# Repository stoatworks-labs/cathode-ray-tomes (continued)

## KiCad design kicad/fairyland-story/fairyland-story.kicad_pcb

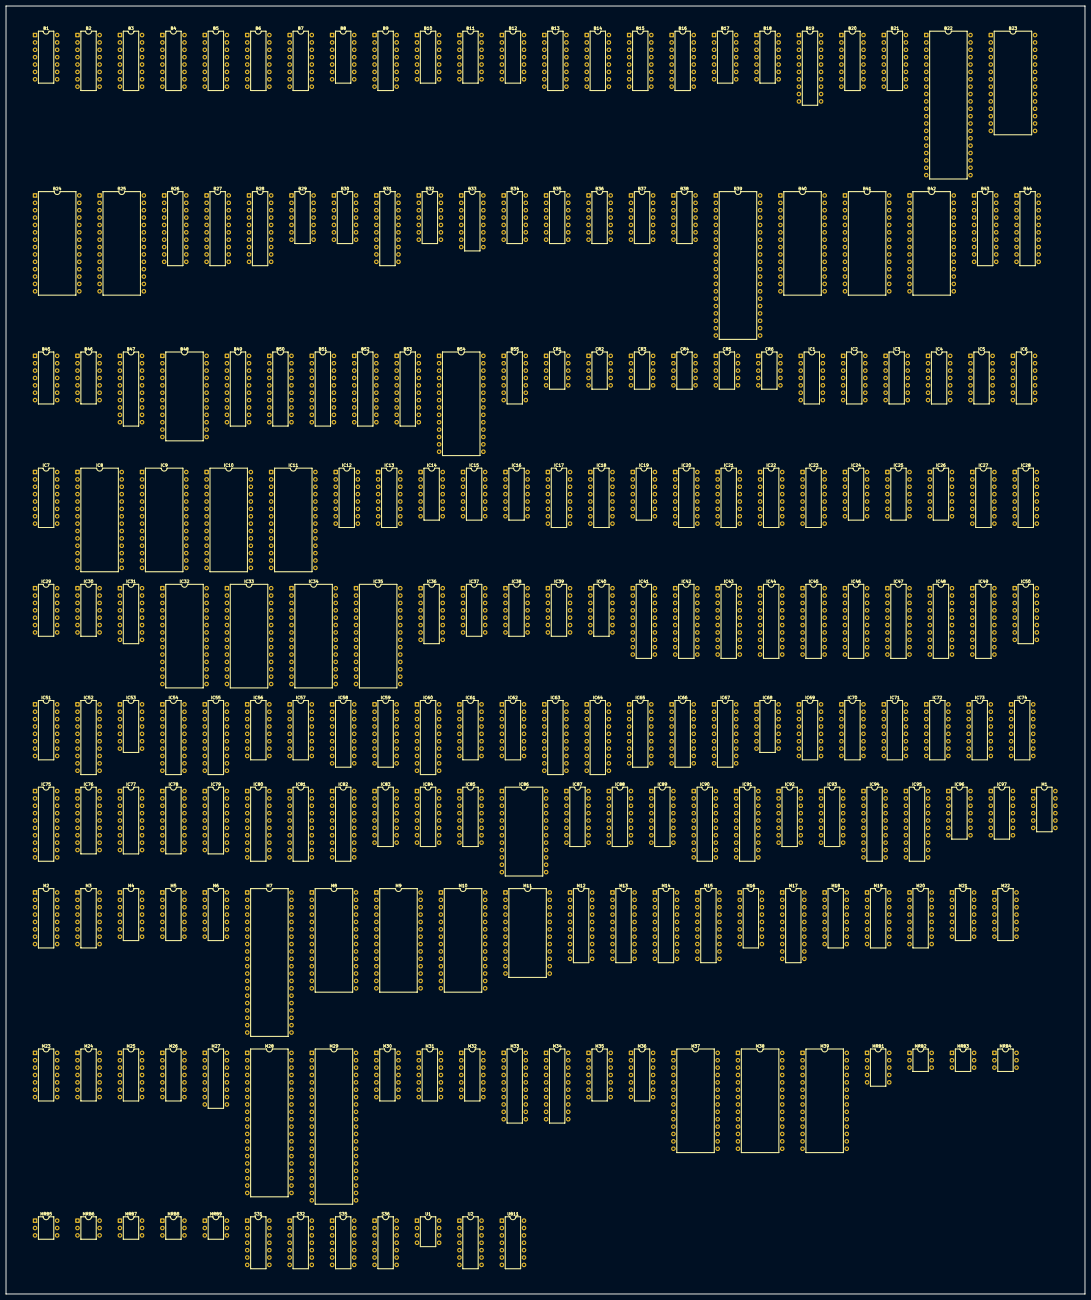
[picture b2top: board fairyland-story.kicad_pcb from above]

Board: 2 copper layers, 371.7 x 443.7 mm, 213 parts (0 on the bottom side), 719 nets, no tracks yet.

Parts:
B1, B11: 74LS07; DIP-14_W7.62mm
B2: 74LS175; DIP-16_W7.62mm
B3: MC14584B; DIP-16_W7.62mm
B4: TD62003P; DIP-16_W7.62mm
B5, B6, B7, B13, B14, B15: 74LS251; DIP-16_W7.62mm
B8: 74LS393; DIP-14_W7.62mm
B9: 74LS155; DIP-16_W7.62mm
B10, B29: 74LS08; DIP-14_W7.62mm
B12, B34, B35, B36, B37, B46: 74LS74; DIP-14_W7.62mm
B16: 74LS253; DIP-16_W7.62mm
B17, B45: 74LS04; DIP-14_W7.62mm
B18: 74LS10; DIP-14_W7.62mm
B19, B31, B47, B49, B50, B51: 74LS244; DIP-20_W7.62mm
B20, B21, B33: 74LS139; DIP-16_W7.62mm
B22, B39: Z80CPU; DIP-40_W15.24mm
B23, B24, B25, B40, B41, B42: 27128; DIP-28_W15.24mm
B26, B27, B28: 74LS245; DIP-20_W7.62mm
B30: 74LS00; DIP-14_W7.62mm
B32, B55: 74LS02; DIP-14_W7.62mm
B38: 74LS32; DIP-14_W7.62mm
B43, B44, B52, B53: 74LS374; DIP-20_W7.62mm
B48: TMM2018_25_35_45; DIP-24_W15.24mm
B54: MC68705P5S; DIP-28_W15.24mm
CR1, CR2, CR3, CR4, CR5, CR6: XXCRXXXX; DIP-10_W7.62mm
IC1, IC29, IC37: 74LS04; DIP-14_W7.62mm
IC2: 74LS107; DIP-14_W7.62mm
IC3, IC5, IC14, IC19, IC24: 74LS74; DIP-14_W7.62mm
IC4: 74LS125; DIP-14_W7.62mm
IC6, IC16, IC26, IC30, IC38, IC39: 74LS86; DIP-14_W7.62mm
IC7, IC21, IC31, IC61, IC62: 74LS298; DIP-16_W7.62mm
IC8, IC9, IC10, IC11, IC32, IC33, IC34, IC35: 27128; DIP-28_W15.24mm
IC12, IC13, IC22, IC23: 74LS194; DIP-16_W7.62mm
IC15, IC68, IC96: 74LS08; DIP-14_W7.62mm
IC17, IC18, IC27, IC28: 74LS161; DIP-16_W7.62mm
IC20, IC89: 74LS139; DIP-16_W7.62mm
IC25: 74LS10; DIP-14_W7.62mm
IC36: 74LS158; DIP-16_W7.62mm
IC40: 74LS20; DIP-14_W7.62mm
IC41, IC42: 74LS373; DIP-20_W7.62mm
IC43, IC46, IC47, IC52, IC54, IC55: 74LS273; DIP-20_W7.62mm
IC44, IC48, IC63, IC64, IC81, IC95: 74LS374; DIP-20_W7.62mm
IC45, IC90, IC91, IC94: 74LS245; DIP-20_W7.62mm
IC49, IC60, IC75, IC80, IC82: 74LS244; DIP-20_W7.62mm
IC50, IC51: 74LS669; DIP-16_W7.62mm
IC53, IC97: 74LS32; DIP-14_W7.62mm
IC56, IC57: 74LS283; DIP-16_W7.62mm
IC58, IC59, IC65, IC66, IC67, IC76, IC77, IC78, IC79: MBM2148; DIP-18_W7.62mm
IC69: 74LS257; DIP-16_W7.62mm
IC70: 74LS42; DIP-16_W7.62mm
IC71, IC83, IC84, IC85: 74LS157; DIP-16_W7.62mm
IC72, IC73, IC87, IC88: 74LS253; DIP-16_W7.62mm
IC74: 74LS191; DIP-16_W7.62mm
IC86: RAM_2016; DIP-24_W15.24mm
IC92, IC93: 74LS174; DIP-16_W7.62mm
M1: SB3731; DIP-12_W7.62mm
M2, M3: TA7630P; DIP-16_W7.62mm
M4, M5, M6: MC3301P; DIP-14_W7.62mm
M7: Z80CPU; DIP-40_W15.24mm
M8, M9, M10, M37, M38, M39: 2764; DIP-28_W15.24mm
M11: MSM2128-20RS; DIP-24_W15.24mm
M12, M13, M15, M17: 74LS374; DIP-20_W7.62mm
M14, M33, M34: 74LS273; DIP-20_W7.62mm
M16: 74LS367; DIP-16_W7.62mm
M18, M20: 74LS139; DIP-16_W7.62mm
M19: 74LS138; DIP-16_W7.62mm
M21: 74LS32; DIP-14_W7.62mm
M22, M24, M25, M26, M30, M35: 74LS74; DIP-14_W7.62mm
M23: 74LS08; DIP-14_W7.62mm
M27: 74LS155; DIP-16_W7.62mm
M28: YM2149; DIP-40_W15.24mm
M29: MSM5232RS; DIP-42_W15.24mm
M31, M32: 74LS393; DIP-14_W7.62mm
M36: 74LS04; DIP-14_W7.62mm
MRB1: DIP-10_W7.62mm
MRB2, MRB3, MRB4, MRB5, MRB6, MRB7, MRB8, MRB9: DIP-6_W7.62mm
S31, S32: 74LS393; DIP-14_W7.62mm
S35: 74LS74; DIP-14_W7.62mm
S36: 74LS04; DIP-14_W7.62mm
U1: MC1455P; DIP-8_W7.62mm
U2: 74LS07; DIP-14_W7.62mm
UB11: 74LS07; DIP-14_W7.62mm

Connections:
+12V: B1.14, B2.16, B3.14, B3.16, B4.9, B5.16, B6.16, B7.16, B8.14, B9.16, B10.14, B12.1, B12.14, B13.16, B14.16, B15.16, B16.16, B17.14, B18.14, B19.20, B21.16, B22.11, B23.1, B23.28, B24.1, B24.28, B25.1, B25.28, B29.14, B30.14, B31.20, B32.14, B33.16, B34.14, B35.1, B35.13, B35.14, B36.1, B36.13, B36.14, B37.1, B37.13, B37.14, B38.14, B39.11, B40.1, B40.28, B41.1, B41.28, B42.1, B42.28, B45.14, B46.1, B46.4, B46.10, B46.13, B46.14, B47.20, B48.24, B49.20, B50.20, B51.20, B54.3, B54.6, B55.14, CR1.1, CR2.1, CR3.1, CR4.1, CR5.1, CR6.1, IC1.14, IC2.4, IC2.10, IC2.11, IC2.13, IC2.14, IC3.1, IC3.4, IC3.13, IC5.1, IC5.4, IC5.10, IC5.13, IC5.14, IC6.14, IC7.16, IC8.1, IC8.27, IC8.28, IC9.1, IC9.27, IC9.28, IC10.1, IC10.27, IC10.28, IC11.1, IC11.27, IC11.28, IC12.1, IC13.1, IC14.4, IC14.14, IC15.14, IC16.14, IC17.1, IC17.5, IC17.6, IC18.1, IC18.9, IC19.4, IC19.10, IC19.13, IC20.16, IC21.16, IC22.1, IC23.1, IC24.1, IC24.10, IC24.13, IC24.14, IC25.11, IC25.14, IC26.14, IC27.1, IC27.3, IC27.4, IC27.5, IC28.1, IC28.5, IC29.14, IC30.14, IC31.6, IC31.16, IC32.1, IC32.27, IC32.28, IC33.1, IC33.27, IC33.28, IC34.1, IC34.27, IC34.28, IC35.1, IC35.27, IC35.28, IC36.16, IC37.14, IC38.14, IC39.14, IC40.14, IC41.20, IC42.20, IC43.1, IC46.1, IC47.1, IC49.20, IC50.16, IC51.16, IC53.14, IC54.1, IC55.1, IC58.18, IC59.18, IC60.20, IC61.16, IC62.16, IC65.18, IC66.18, IC67.18, IC68.14, IC69.2, IC69.5, IC70.16, IC71.2, IC71.5, IC71.13, IC72.16, IC73.3, IC73.4, IC73.10, IC73.12, IC73.13, IC73.16, IC74.1, IC74.5, IC74.10, IC74.15, IC74.16, IC75.20, IC76.18, IC77.18, IC78.18, IC79.18, IC80.20, IC82.20, IC83.13, IC87.16, IC88.4, IC88.13, IC88.16, IC89.16, IC92.16, IC93.16, IC96.14, IC97.14, M2.12, M3.12, M4.14, M5.14, M6.14, M7.11, M8.1, M8.27, M8.28, M9.1, M9.27, M9.28, M10.1, M10.27, M10.28, M11.24, M14.1, M16.16, M18.16, M19.6, M20.16, M21.14, M22.10, M22.14, M23.14, M26.1, M26.10, M26.13, M26.14, M27.16, M28.25, M28.28, M28.40, M30.4, M30.10, M30.12, M30.14, M33.1, M34.1, M35.4, M35.10, M35.13, M37.1, M37.27, M37.28, M38.1, M38.27, M38.28, M39.1, M39.27, M39.28, S31.14, S32.14, S35.14, S36.14, U1.4, U1.8
/COINLOCK: B2.2, B11.1, B11.13
/Cabinet/CR1P_BTN_1: B14.15, CR6.2
/Cabinet/CR1P_BTN_2: B13.15, CR6.6
/Cabinet/CR1P_DOWN: B7.15, CR3.4
/Cabinet/CR1P_LEFT: B5.15, CR3.8
/Cabinet/CR1P_RIGHT: B6.15, CR3.6
/Cabinet/CR1P_START: B13.1, CR1.2
/Cabinet/CR1P_UP: B15.15, CR3.2
/Cabinet/CR2P_BTN_1: B14.13, CR6.4
/Cabinet/CR2P_BTN_2: B13.13, CR6.8
/Cabinet/CR2P_DOWN: B7.13, CR2.4
/Cabinet/CR2P_LEFT: B5.13, CR2.8
/Cabinet/CR2P_RIGHT: B6.13, CR2.6
/Cabinet/CR2P_START: B14.1, CR1.4
/Cabinet/CR2P_UP: B15.13, CR2.2
/Cabinet/CRNC1: B15.12, CR5.2
/Cabinet/CRNC2: B7.12, CR5.4
/Cabinet/CRNC3: B6.12, CR5.6
/Cabinet/CRNC4: B5.12, CR5.8
/Cabinet/CRNC5: B15.14, CR4.2
/Cabinet/CRNC6: B7.14, CR4.4
/Cabinet/CRNC7: B6.14, CR4.6
/Cabinet/CRNC8: B5.14, CR4.8
/Cabinet/CRSERVICE: B15.1, CR1.6
/Cabinet/CRTILT: B7.1, CR1.8
/Cabinet/~COINA: B10.6, B11.5
/Cabinet/~COINAB: B4.1, B4.2, B5.1, B11.6
/Cabinet/~COINB: B10.8, B11.9
/Cabinet/~COINBB: B4.4, B4.5, B6.1, B11.8
/Cabinet/~COIN_2: B3.6, B16.13
/MAB0: B39.30, B40.10, B41.10, B42.10, B43.9, B49.2
/MAB1: B39.31, B40.9, B41.9, B42.9, B43.12, B49.4
/MAB2: B39.32, B40.8, B41.8, B42.8, B43.6, B49.6
/MAB3: B39.33, B40.7, B41.7, B42.7, B43.15, B49.8
/MAB4: B39.34, B40.6, B41.6, B42.6, B43.5, B50.2
/MAB5: B39.35, B40.5, B41.5, B42.5, B43.16, B50.4
/MAB6: B39.36, B40.4, B41.4, B42.4, B43.2, B50.6
/MAB7: B39.37, B40.3, B41.3, B42.3, B43.19, B50.8
/MAB8: B39.38, B40.25, B41.25, B42.25, B44.9, B51.2
/MAB9: B39.39, B40.24, B41.24, B42.24, B44.12, B51.4
/MAB10: B39.40, B40.21, B41.21, B42.21, B44.6, B51.6
/MAB11: B39.1, B40.23, B41.23, B42.23, B44.15, B51.8
/MAB12: B19.11, B21.2, B39.2, B40.2, B41.2, B42.2, B44.5
/MAB13: B21.3, B39.3, B40.26, B41.26, B42.26, B44.16
/MAB14: B21.14, B39.4, B44.2
/MAB15: B21.13, B39.5, B44.19
/MD0: B27.9, B28.11, B39.14, B40.11, B41.11, B42.11
/MD1: B27.8, B28.12, B39.15, B40.12, B41.12, B42.12
/MD2: B27.7, B28.13, B39.12, B40.13, B41.13, B42.13
/MD3: B27.6, B28.14, B39.8, B40.15, B41.15, B42.15
/MD4: B27.5, B28.15, B39.7, B40.16, B41.16, B42.16
/MD5: B27.4, B28.16, B39.9, B40.17, B41.17, B42.17
/MD6: B27.3, B28.17, B39.10, B40.18, B41.18, B42.18
/MD7: B27.2, B28.18, B39.13, B40.19, B41.19, B42.19
/Main/CLK5: B46.9, B47.6
/Main/MCU/IBF: B12.9, B54.8
/Main/MCU/PA0: B28.9, B43.8, B44.8, B52.8, B53.12, B54.20
/Main/MCU/PA1: B28.8, B43.13, B44.13, B52.13, B53.9, B54.21
/Main/MCU/PA2: B28.7, B43.7, B44.7, B52.7, B53.15, B54.22
/Main/MCU/PA3: B28.6, B43.14, B44.14, B52.14, B53.6, B54.23
/Main/MCU/PA4: B28.5, B43.4, B44.4, B52.4, B53.16, B54.24
/Main/MCU/PA5: B28.4, B43.17, B44.17, B52.17, B53.5, B54.25
/Main/MCU/PA6: B28.3, B43.3, B44.3, B52.3, B53.19, B54.26
/Main/MCU/PA7: B28.2, B43.18, B44.18, B52.18, B53.2, B54.27
/Main/MCU/~ALE0: B43.11, B54.18
/Main/MCU/~ALE1: B44.11, B54.19
/Main/MCU/~LRD: B12.11, B53.1, B54.13
/Main/MCU/~LWR: B12.3, B52.11, B54.14
/Main/MCU/~OBF: B12.5, B54.9
/Main/MQpC: B30.2, B30.10, B32.13, B36.10
/Main/MxC: B30.1, B34.5
/Main/SMRQ: B30.4, B30.13, B32.1
/Main/SWAIT: B29.1, B35.9
/Main/~BUSRQ: B18.2, B39.25, B54.15
/Main/~CLK5: B46.8, B46.12, B47.8
/Main/~CLK5*: B34.11, B36.11, B47.4, B47.12
/Main/~CRD: B47.15, B54.17
/Main/~CWR: B28.1, B47.17, B54.16
/Main/~INT: B37.9, B39.16
/Main/~IORQ: B38.12, B39.20
/Main/~M1: B38.13, B39.27
/Main/~MCLK: B39.6, B46.3, B47.18
/Main/~MCU: B18.1, B28.19, B43.1, B44.1, B46.6, B47.19, B54.10
/Main/~MMpC: B17.1, B21.1, B21.9, B32.12
/Main/~MMx0: B21.12, B40.20
/Main/~MMx4: B21.11, B41.20
/Main/~MMx8: B21.10, B42.20
/Main/~MREQ: B32.11, B39.19, B47.7
/Main/~MSpC': B34.13, B35.3
/Main/~MxC: B30.9, B34.6, B35.10
/Main/~SOECLK: B34.3, B47.2, B47.14
/OBF: B12.6, B14.14
/SBA0: B22.30, B23.10, B24.10, B25.10, B49.17
/SBA1: B22.31, B23.9, B24.9, B25.9, B49.15
/SBA2: B22.32, B23.8, B24.8, B25.8, B49.13
/SBA3: B22.33, B23.7, B24.7, B25.7, B49.11
/SBA4: B22.34, B23.6, B24.6, B25.6, B50.17
/SBA5: B22.35, B23.5, B24.5, B25.5, B50.15
/SBA6: B22.36, B23.4, B24.4, B25.4, B50.13
/SBA7: B22.37, B23.3, B24.3, B25.3, B50.11
/SBA8: B22.38, B23.25, B24.25, B25.25, B51.11
/SBA9: B22.39, B23.24, B24.24, B25.24, B51.13
/SBA10: B22.40, B23.21, B24.21, B25.21, B51.15
/SBA11: B22.1, B23.23, B24.23, B25.23, B51.17
/SBA12: B19.8, B22.2, B23.2, B24.2, B25.2, B33.2
/SBA13: B22.3, B23.26, B24.26, B25.26, B33.3
/SBA14: B22.4, B33.13
/SBA15: B22.5, B33.14
/SBCLK: B22.6, B47.16
/SBD0: B22.14, B23.11, B24.11, B25.11, B26.9
/SBD1: B22.15, B23.12, B24.12, B25.12, B26.8
/SBD2: B22.12, B23.13, B24.13, B25.13, B26.7
/SBD3: B22.8, B23.15, B24.15, B25.15, B26.6
/SBD4: B22.7, B23.16, B24.16, B25.16, B26.5
/SBD5: B22.9, B23.17, B24.17, B25.17, B26.4
/SBD6: B22.10, B23.18, B24.18, B25.18, B26.3
/SBD7: B22.13, B23.19, B24.19, B25.19, B26.2
/SHAB0: B5.11, B6.11, B7.11, B9.13, B13.11, B14.11, B15.11, B16.14, B48.8, B49.3, B49.18, IC60.2, IC75.8, IC80.8, IC85.2, IC89.14, M18.2, M18.14
/SHAB1: B5.10, B6.10, B7.10, B9.3, B13.10, B14.10, B15.10, B16.2, B48.7, B49.5, B49.16, IC60.4, IC75.6, IC80.6, IC85.5, IC89.13
/SHAB2: B5.9, B6.9, B7.9, B13.9, B14.9, B15.9, B48.6, B49.7, B49.14, IC60.6, IC75.4, IC80.4, IC85.11
/SHAB3: B48.5, B49.9, B49.12, IC60.8, IC75.2, IC80.2, IC85.14
/SHAB4: B48.4, B50.3, B50.18, IC60.11, IC75.17, IC80.17, IC84.2
/SHAB5: B48.3, B50.5, B50.16, IC60.13, IC75.15, IC80.15, IC84.5
/SHAB6: B48.2, B50.7, B50.14, IC60.15, IC75.13, IC80.13, IC84.11
/SHAB7: B48.1, B50.9, B50.12, IC60.17, IC75.11, IC80.11, IC84.14
/SHAB8: B48.23, B51.3, B51.18, IC83.2, IC89.2
/SHAB9: B48.22, B51.5, B51.16, IC83.5, IC89.3
/SHAB10: B20.2, B48.19, B51.7, B51.14, IC83.11
/SHAB11: B20.3, B51.9, B51.12
/SHDB0: B2.4, B13.5, B26.18, B27.18, B48.9, B52.9, B53.13
/SHDB1: B2.5, B14.5, B26.17, B27.17, B48.10, B52.12, B53.8
/SHDB2: B2.12, B15.5, B26.16, B27.16, B48.11, B52.6, B53.14
/SHDB3: B2.13, B7.5, B26.15, B27.15, B48.13, B52.15, B53.7
/SHDB4: B6.5, B26.14, B27.14, B48.14, B52.5, B53.17
/SHDB5: B5.5, B26.13, B27.13, B48.15, B52.16, B53.4
/SHDB6: B16.7, B26.12, B27.12, B48.16, B52.2, B53.18
/SHDB7: B16.9, B26.11, B27.11, B48.17, B52.19, B53.3
/Shared/?: B31.5, B31.16
/Shared/~CTL: B2.9, B9.5
/Shared/~SHACS: B19.5, B19.16, B48.18
/Sound/AMUTE: M1.6, M22.9
/Sound/AVSS: M29.23, M29.32
/Sound/CLK2: M28.22, M29.19, M29.20, M32.3
/Sound/CLK4: M29.13, M35.5
/Sound/Latches/~NMIdis: M22.3, M27.11
/Sound/Latches/~NMIsen: M22.4, M22.11, M27.10
/Sound/Latches/~RST_CS: M18.5, M30.3
/Sound/Latches/~SD2SH: M15.11, M25.10, M27.9
/Sound/Latches/~SDCHK: M12.1, M25.3, M27.7
/Sound/Latches/~SDOE': M13.1, M27.4
/Sound/Latches/~SDST: M16.1, M27.6
/Sound/Latches/~SH2SD: M12.11, M18.4, M25.4
/Sound/Latches/~SHA3: M17.11, M24.4
/Sound/Latches/~SHAOE3: M17.1, M24.3, M27.5
/Sound/Latches/~SHCHK: M18.12, M25.11
/Sound/Latches/~SHST: M16.15, M18.11
/Sound/PSG: M28.3, M28.4, M28.38
/Sound/SA0: M7.30, M8.10, M9.10, M10.10, M11.8, M21.5, M29.17, M37.10, M38.10, M39.10
/Sound/SA1: M7.31, M8.9, M9.9, M10.9, M11.7, M29.16, M37.9, M38.9, M39.9
/Sound/SA2: M7.32, M8.8, M9.8, M10.8, M11.6, M29.15, M37.8, M38.8, M39.8
/Sound/SA3: M7.33, M8.7, M9.7, M10.7, M11.5, M29.14, M37.7, M38.7, M39.7
/Sound/SA4: M7.34, M8.6, M9.6, M10.6, M11.4, M37.6, M38.6, M39.6
/Sound/SA5: M7.35, M8.5, M9.5, M10.5, M11.3, M37.5, M38.5, M39.5
/Sound/SA6: M7.36, M8.4, M9.4, M10.4, M11.2, M37.4, M38.4, M39.4
/Sound/SA7: M7.37, M8.3, M9.3, M10.3, M11.1, M37.3, M38.3, M39.3
/Sound/SA8: M7.38, M8.25, M9.25, M10.25, M11.23, M37.25, M38.25, M39.25
/Sound/SA9: M7.39, M8.24, M9.24, M10.24, M11.22, M20.2, M27.13, M37.24, M38.24, M39.24
/Sound/SA10: M7.40, M8.21, M9.21, M10.21, M11.19, M20.3, M27.3, M37.21, M38.21, M39.21
/Sound/SA11: M7.1, M8.23, M9.23, M10.23, M20.14, M37.23, M38.23, M39.23
/Sound/SA12: M7.2, M8.2, M9.2, M10.2, M20.13, M37.2, M38.2, M39.2
/Sound/SA13: M7.3, M10.26, M19.1
/Sound/SA14: M7.4, M19.2
/Sound/SA15: M7.5, M19.3
/Sound/SBD0: M12.18, M15.12, M16.11, M30.2
/Sound/SBD1: M12.3, M15.9, M16.13
/Sound/SBD2: M12.17, M15.15
/Sound/SBD3: M12.4, M15.6
/Sound/SBD4: M12.14, M15.16
/Sound/SBD5: M12.7, M15.5
/Sound/SBD6: M12.13, M15.19
/Sound/SD0: M7.14, M8.11, M9.11, M10.11, M11.9, M12.19, M13.18, M13.19, M15.13, M16.7, M17.12, M37.11, M38.11, M39.11
/Sound/SD1: M7.15, M8.12, M9.12, M10.12, M11.10, M12.2, M13.2, M13.3, M15.8, M16.5, M17.9, M37.12, M38.12, M39.12
/Sound/SD2: M7.12, M8.13, M9.13, M10.13, M11.11, M12.16, M13.16, M13.17, M15.14, M16.3, M17.15, M37.13, M38.13, M39.13
/Sound/SD3: M7.8, M8.15, M9.15, M10.15, M11.13, M12.5, M13.4, M13.5, M15.7, M17.6, M37.15, M38.15, M39.15
/Sound/SD4: M7.7, M8.16, M9.16, M10.16, M11.14, M12.15, M13.14, M13.15, M15.17, M17.16, M37.16, M38.16, M39.16
/Sound/SD5: M7.9, M8.17, M9.17, M10.17, M11.15, M12.6, M13.6, M13.7, M15.4, M17.5, M37.17, M38.17, M39.17
/Sound/SD6: M7.10, M8.18, M9.18, M10.18, M11.16, M12.12, M13.12, M13.13, M15.18, M17.19, M37.18, M38.18, M39.18
/Sound/SD7: M7.13, M8.19, M9.19, M10.19, M11.17, M12.9, M13.8, M13.9, M15.3, M17.2, M22.12, M37.19, M38.19, M39.19
/Sound/Sound Generators/BAL0: M33.19, MRB7.2
/Sound/Sound Generators/BAL1: M33.2, MRB7.3
/Sound/Sound Generators/BAL2: M33.16, MRB7.4
/Sound/Sound Generators/BAL3: M33.5, MRB7.5
/Sound/Sound Generators/BASS0: M34.19, MRB9.2
/Sound/Sound Generators/BASS1: M34.2, MRB9.3
/Sound/Sound Generators/BASS2: M34.16, MRB9.4
/Sound/Sound Generators/BASS3: M34.5, MRB9.5
/Sound/Sound Generators/BC1: M28.29, S36.4
/Sound/Sound Generators/BDIR: M28.27, S36.2
/Sound/Sound Generators/TRB0: M34.12, MRB8.2
/Sound/Sound Generators/TRB1: M34.6, MRB8.3
/Sound/Sound Generators/TRB2: M34.15, MRB8.4
/Sound/Sound Generators/TRB3: M34.9, MRB8.5
/Sound/Sound Generators/VDD: M29.3, M29.41
/Sound/Sound Generators/VOL0: M33.12, MRB6.2
/Sound/Sound Generators/VOL1: M33.6, MRB6.3
/Sound/Sound Generators/VOL2: M33.15, MRB6.4
/Sound/Sound Generators/VOL3: M33.9, MRB6.5
/Sound/Sound Generators/~CFG0: M20.6, M33.11
/Sound/Sound Generators/~CFG1: M20.7, M34.11
/Sound/SÐ0: M14.18, M28.37, M29.11, M33.18, M34.18
/Sound/SÐ1: M14.3, M28.36, M29.10, M33.3, M34.3
/Sound/SÐ2: M14.17, M28.35, M29.9, M33.17, M34.17
/Sound/SÐ3: M14.4, M28.34, M29.8, M33.4, M34.4
/Sound/SÐ4: M14.14, M28.33, M29.7, M33.13, M34.13
/Sound/SÐ5: M14.7, M28.32, M29.6, M33.7, M34.7
/Sound/SÐ6: M14.13, M28.31, M29.5, M33.14, M34.14
/Sound/SÐ7: M14.8, M28.30, M29.4, M33.8, M34.8
/Sound/TONEA: M29.28, M29.29, M29.30, M29.31
/Sound/TONEB: M29.33, M29.34, M29.35, M29.36
/Sound/~COMM: M20.9, M27.15, S36.5
/Sound/~INT: M7.16, M30.8
/Sound/~IORQ: M7.20, M21.12
/Sound/~M1: M7.27, M21.13
/Sound/~MSM: M20.5, M29.12, M35.1
/Sound/~NMI: M7.17, M21.8
/Sound/~ONGEN: M20.1, M21.3
/Sound/~RAM: M11.18, M20.12
/Sound/~RST: M7.26, M22.1, M22.13, M23.8, M24.1, M25.1, M25.13, M28.23, M29.18
/Sound/~SCE0: M8.20, M19.15
/Sound/~SCE1: M9.20, M19.14
/Sound/~SCE2: M10.20, M19.13
/Sound/~SCE3: M19.12, M37.20
/Sound/~SCE4: M19.11, M38.20
/Sound/~SCE5: M19.10, M39.20
/Sound/~SCE6: M19.9, M20.15
/Sound/~SCLK: M7.6, M36.12
/Sound/~SRD: M7.21, M8.22, M9.22, M10.22, M11.20, M27.2, M37.22, M38.22, M39.22
/Sound/~SWR: M7.22, M11.21, M21.1, M27.14
/Sound/~VDAC: M13.11, M14.11, M27.12
/Sound/~WAIT: M7.24, M26.5, M26.12
/Sub/~MSx0: B23.20, B33.12
/Sub/~MSx4: B24.20, B33.11
/Sub/~SBINT: B22.16, B37.5
/Sub/~SBIORQ: B22.20, B25.20, B38.1, B45.11
/VBLK: B8.13, B37.3, B37.11
/Video/BBANK0: IC46.5, IC61.3
/Video/BBANK1: IC46.15, IC61.4
/Video/BGFLIP_EN: IC15.10, IC15.12, IC46.16
/Video/BPRIO0: IC52.14, IC54.19
/Video/BPRIO1: IC52.13, IC54.16
/Video/CA0: IC6.3, IC8.10, IC9.10, IC10.10, IC11.10, IC32.10, IC33.10, IC34.10, IC35.10
/Video/CA1: IC6.11, IC8.9, IC9.9, IC10.9, IC11.9, IC32.9, IC33.9, IC34.9, IC35.9
/Video/CA2: IC6.6, IC8.8, IC9.8, IC10.8, IC11.8, IC32.8, IC33.8, IC34.8, IC35.8
/Video/CA3: IC6.8, IC8.7, IC9.7, IC10.7, IC11.7, IC32.7, IC33.7, IC34.7, IC35.7
/Video/CA4: IC7.15, IC8.6, IC9.6, IC10.6, IC11.6, IC32.6, IC33.6, IC34.6, IC35.6
/Video/CA5: IC7.14, IC8.5, IC9.5, IC10.5, IC11.5, IC32.5, IC33.5, IC34.5, IC35.5
/Video/CA6: IC7.13, IC8.4, IC9.4, IC10.4, IC11.4, IC32.4, IC33.4, IC34.4, IC35.4
/Video/CA7: IC7.12, IC8.3, IC9.3, IC10.3, IC11.3, IC32.3, IC33.3, IC34.3, IC35.3
/Video/CA8: IC8.25, IC9.25, IC10.25, IC11.25, IC21.15, IC32.25, IC33.25, IC34.25, IC35.25
/Video/CA9: IC8.24, IC9.24, IC10.24, IC11.24, IC21.14, IC32.24, IC33.24, IC34.24, IC35.24
/Video/CA10: IC8.21, IC9.21, IC10.21, IC11.21, IC21.13, IC32.21, IC33.21, IC34.21, IC35.21
/Video/CA11: IC8.23, IC9.23, IC10.23, IC11.23, IC21.12, IC32.23, IC33.23, IC34.23, IC35.23
/Video/CA12: IC8.2, IC9.2, IC10.2, IC11.2, IC31.15, IC32.2, IC33.2, IC34.2, IC35.2
/Video/CA13: IC8.26, IC9.26, IC10.26, IC11.26, IC31.14, IC32.26, IC33.26, IC34.26, IC35.26
/Video/CLK6M: IC2.3, IC2.8, IC12.11, IC13.11, IC22.11, IC23.11
/Video/DB0: IC4.8, IC41.19, IC42.19, IC45.2, IC46.18, IC90.9, IC91.9, IC94.9
/Video/DB1: IC41.2, IC42.2, IC45.3, IC46.3, IC90.8, IC91.8, IC94.8
/Video/DB2: IC41.16, IC42.16, IC45.4, IC46.17, IC90.7, IC91.7, IC94.7
/Video/DB3: IC41.5, IC42.5, IC45.5, IC46.4, IC90.6, IC91.6, IC94.6
/Video/DB4: IC41.15, IC42.15, IC45.6, IC46.14, IC90.5, IC91.5, IC94.5
/Video/DB5: IC41.6, IC42.6, IC45.7, IC46.7, IC90.4, IC91.4, IC94.4
/Video/DB6: IC41.12, IC42.12, IC45.8, IC46.13, IC90.3, IC91.3, IC94.3
/Video/DB7: IC41.9, IC42.9, IC45.9, IC46.8, IC90.2, IC91.2, IC94.2
/Video/GHFLIP: IC14.2, IC38.5, IC46.19
/Video/GVFLIP: IC16.1, IC16.4, IC16.10, IC16.13, IC26.1, IC26.4, IC26.10, IC26.13, IC46.2
/Video/H0: IC5.5, IC18.7, IC18.10, IC28.7, IC70.15, IC72.14, IC73.14, IC87.14, IC88.14
/Video/H1: IC18.14, IC42.3, IC70.14, IC87.3, IC87.5, IC88.10
/Video/H2: IC14.13, IC18.13, IC42.17, IC68.12, IC70.13, IC87.11
/Video/H3: IC18.12, IC39.4, IC42.4
/Video/H4: IC18.11, IC19.3, IC39.12, IC42.14
/Video/H5: IC15.4, IC28.14, IC39.9, IC42.7
/Video/H6: IC28.13, IC29.11, IC39.1, IC42.13
/Video/H7: IC28.12, IC38.1, IC42.8
/Video/H8: IC5.11, IC17.2, IC25.1, IC27.2, IC28.11, IC68.2, IC68.13, IC69.1, IC74.11
/Video/HF3: IC39.6, IC68.1
/Video/HF4: IC39.11, IC87.10
/Video/HF5: IC39.8, IC72.6
/Video/HF6: IC39.3, IC72.10
/Video/HF7: IC38.3, IC88.6
/Video/HOVER: IC68.9, IC74.7
/Video/Line buffer/A0: IC51.14, IC65.5, IC66.5, IC67.5
/Video/Line buffer/A1: IC51.13, IC65.6, IC66.6, IC67.6
/Video/Line buffer/A2: IC51.12, IC65.7, IC66.7, IC67.7
/Video/Line buffer/A3: IC51.11, IC65.4, IC66.4, IC67.4
/Video/Line buffer/A4: IC50.14, IC65.3, IC66.3, IC67.3
/Video/Line buffer/A5: IC50.13, IC65.2, IC66.2, IC67.2
/Video/Line buffer/A6: IC50.12, IC65.1, IC66.1, IC67.1
/Video/Line buffer/A7: IC50.11, IC65.17, IC66.17, IC67.17
/Video/Line buffer/~CLK6M: IC50.2, IC51.2
/Video/Line buffer/~CS: IC65.8, IC66.8, IC67.8, IC96.3
/Video/Line buffer/~HB8*: IC82.2, IC96.2
/Video/OPRIO0: IC47.12, IC82.8
/Video/OPRIO1: IC47.16, IC82.6
/Video/OPRIO2: IC47.19, IC82.4
/Video/OPXL0: IC49.12, IC64.18, IC65.14
/Video/OPXL1: IC49.14, IC64.17, IC65.13
/Video/OPXL2: IC49.16, IC64.14, IC65.12
/Video/OPXL3: IC49.9, IC64.3, IC65.11
/Video/OPXL4: IC49.7, IC64.4, IC66.14
/Video/OPXL5: IC49.5, IC64.7, IC66.13
/Video/OPXL6: IC49.3, IC64.8, IC66.12
/Video/OPXL7: IC49.18, IC64.13, IC66.11
/Video/OPXL8: IC67.14, IC81.7, IC82.12
/Video/OPXL9: IC67.13, IC81.8, IC82.14
/Video/OPXL10: IC67.12, IC82.16, IC95.4
/Video/OPXL11: IC67.11, IC82.18, IC95.3
/Video/ORAMD0: IC7.5, IC43.3, IC44.2, IC44.3, IC45.18, IC57.5, IC58.14, IC62.2
/Video/ORAMD1: IC7.6, IC43.18, IC44.18, IC44.19, IC45.17, IC57.3, IC58.13, IC62.1
/Video/ORAMD2: IC21.2, IC43.4, IC44.4, IC44.5, IC45.16, IC57.14, IC58.12, IC62.5
/Video/ORAMD3: IC21.1, IC43.17, IC44.16, IC44.17, IC45.15, IC57.12, IC58.11, IC62.6
/Video/ORAMD4: IC21.5, IC43.7, IC44.6, IC44.7, IC45.14, IC56.5, IC59.14, IC61.2
/Video/ORAMD5: IC21.6, IC43.14, IC44.14, IC44.15, IC45.13, IC56.3, IC59.13, IC61.1
/Video/ORAMD6: IC43.8, IC44.8, IC44.9, IC45.12, IC56.14, IC59.12, IC61.5
/Video/ORAMD7: IC43.13, IC44.12, IC44.13, IC45.11, IC56.12, IC59.11, IC61.6
/Video/Object RAM/A0: IC58.5, IC59.5, IC60.18, IC87.7
/Video/Object RAM/A1: IC58.6, IC59.6, IC60.16, IC87.9
/Video/Object RAM/A2: IC58.7, IC59.7, IC60.14, IC72.7
/Video/Object RAM/A3: IC58.4, IC59.4, IC60.12, IC72.9
/Video/Object RAM/A4: IC58.3, IC59.3, IC60.9, IC88.7
/Video/Object RAM/A5: IC58.2, IC59.2, IC60.7, IC88.9
/Video/Object RAM/A6: IC58.1, IC59.1, IC60.5, IC73.7
/Video/Object RAM/A7: IC58.17, IC59.17, IC60.3, IC73.9
/Video/Object RAM/CNT0: IC74.3, IC87.12
/Video/Object RAM/CNT1: IC72.4, IC74.2
/Video/Object RAM/CNT2: IC72.12, IC74.6
/Video/Object RAM/DY0: IC55.4, IC57.4
/Video/Object RAM/DY1: IC55.8, IC57.1
/Video/Object RAM/DY2: IC55.3, IC57.13
/Video/Object RAM/DY3: IC55.7, IC57.10
/Video/Object RAM/DY4: IC40.9, IC55.18, IC56.4
/Video/Object RAM/DY5: IC40.13, IC55.13, IC56.1
/Video/Object RAM/DY6: IC40.12, IC55.14, IC56.13
/Video/Object RAM/DY7: IC40.10, IC55.17, IC56.10
/Video/Object RAM/DY_CK: IC55.11, IC69.12
/Video/Object RAM/H2&H8: IC68.11, IC72.2, IC73.2, IC87.2, IC88.2
/Video/Object RAM/IDX0: IC43.2, IC72.5
/Video/Object RAM/IDX1: IC43.19, IC72.11
/Video/Object RAM/IDX2: IC43.5, IC88.5
/Video/Object RAM/IDX3: IC43.16, IC88.11
/Video/Object RAM/IDX4: IC43.6, IC73.5
/Video/Object RAM/IDX_CK: IC44.1, IC71.4, IC74.14
/Video/Object RAM/PAL0: IC47.8, IC62.15
/Video/Object RAM/PAL1: IC47.7, IC62.14
/Video/Object RAM/PAL2: IC47.4, IC62.13
/Video/Object RAM/PAL3: IC47.3, IC62.12
/Video/Object RAM/blink: IC68.8, IC87.4
/Video/Object RAM/odd/even: IC24.9, IC68.10
/Video/Object RAM/~AOE: IC71.7, IC72.1, IC72.15, IC73.1, IC73.15, IC87.1, IC87.15, IC88.1, IC88.15
/Video/Object RAM/~HB8: IC62.10, IC69.4, IC73.6
/Video/Object RAM/~MATCH: IC24.2, IC40.8
/Video/Object RAM/~MATCH*: IC53.9, IC69.7
/Video/Object RAM/~PXLEN*: IC47.14, IC69.9
/Video/Object RAM/~WE: IC58.10, IC59.10, IC71.3, IC71.9
/Video/PH3: IC29.6, IC61.11, IC62.11
/Video/PXL0: IC36.4, IC40.1, IC48.13, IC49.8, IC81.13
/Video/PXL1: IC36.7, IC40.5, IC48.14, IC49.6, IC81.14
/Video/PXL2: IC36.9, IC40.4, IC48.17, IC49.4, IC81.17
/Video/PXL3: IC36.12, IC40.2, IC48.8, IC49.11, IC81.18
/Video/PXL4: IC47.9, IC48.7, IC49.13
/Video/PXL5: IC47.6, IC48.4, IC49.15
/Video/PXL6: IC47.5, IC48.3, IC49.17
/Video/PXL7: IC47.2, IC48.18, IC49.2
/Video/Palette/A0: IC63.19, IC75.12, IC76.5, IC77.5, IC78.5
/Video/Palette/A1: IC63.16, IC75.14, IC76.6, IC77.6, IC78.6
/Video/Palette/A2: IC63.15, IC75.16, IC76.7, IC77.7, IC78.7
/Video/Palette/A3: IC63.2, IC75.18, IC76.4, IC77.4, IC78.4
/Video/Palette/A4: IC63.5, IC75.3, IC76.3, IC77.3, IC78.3
/Video/Palette/A5: IC63.6, IC75.5, IC76.2, IC77.2, IC78.2
/Video/Palette/A6: IC63.9, IC75.7, IC76.1, IC77.1, IC78.1
/Video/Palette/A7: IC63.12, IC75.9, IC76.17, IC77.17, IC78.17
/Video/Palette/A8: IC76.16, IC77.16, IC78.16, IC82.3, IC95.16
/Video/Palette/CLK6M: IC48.11, IC63.11, IC64.11, IC81.11, IC92.9, IC93.9
/Video/Palette/D0: IC76.14, IC91.11, IC92.11
/Video/Palette/D1: IC76.13, IC91.12, IC92.13
/Video/Palette/D2: IC76.12, IC91.13, IC92.14
/Video/Palette/D3: IC76.11, IC91.14, IC92.6
/Video/Palette/D4: IC77.14, IC91.15, IC92.4
/Video/Palette/D5: IC77.13, IC91.16, IC92.3
/Video/Palette/D6: IC77.12, IC91.17, IC93.13
/Video/Palette/D7: IC77.11, IC91.18, IC93.14
/Video/Palette/D8: IC78.14, IC93.3, IC94.11
/Video/Palette/D9: IC78.13, IC93.4, IC94.12
/Video/Palette/D10: IC78.12, IC93.6, IC94.13
/Video/Palette/D11: IC78.11, IC93.11, IC94.14
/Video/Palette/D12: IC79.14, IC94.15, IC96.12
/Video/Palette/D13: IC79.13, IC94.16
/Video/Palette/D14: IC79.12, IC94.17
/Video/Palette/D15: IC79.11, IC94.18
/Video/Palette/IC52_9: IC52.9, IC95.14
/Video/Palette/IC95_8: IC25.10, IC95.8, IC95.12
/Video/Palette/IC95_9: IC25.9, IC95.9
/Video/Palette/IC95_15: IC95.13, IC95.15
/Video/Palette/MAxDD/E: IC37.12, IC63.1, IC81.1
/Video/Palette/OBJWIN: IC37.11, IC48.1, IC95.17, IC96.11
/Video/Palette/PAL0: IC48.12, IC63.18, IC64.19
/Video/Palette/PAL1: IC48.15, IC63.17, IC64.16
/Video/Palette/PAL2: IC48.16, IC63.14, IC64.15
/Video/Palette/PAL3: IC48.9, IC63.3, IC64.2
/Video/Palette/PAL4: IC48.6, IC63.4, IC64.5
/Video/Palette/PAL5: IC48.5, IC63.7, IC64.6
/Video/Palette/PAL6: IC48.2, IC63.8, IC64.9
/Video/Palette/PAL7: IC48.19, IC63.13, IC64.12
/Video/Palette/PBANK0: IC46.6, IC82.15, IC82.17
/Video/Palette/PBANK1: IC46.12, IC76.15, IC77.15, IC78.15, IC79.15
/Video/Palette/PRA0: IC79.5, IC80.12, IC81.12
/Video/Palette/PRA1: IC79.6, IC80.14, IC81.15
/Video/Palette/PRA2: IC79.7, IC80.16, IC81.16
/Video/Palette/PRA3: IC79.4, IC80.18, IC81.19
/Video/Palette/PRA4: IC79.3, IC80.3, IC81.2
/Video/Palette/PRA4*: IC52.15, IC81.3
/Video/Palette/PRA5: IC79.2, IC80.5, IC81.5
/Video/Palette/PRA5*: IC52.12, IC81.4
/Video/Palette/PRA6: IC79.1, IC80.7, IC81.6
/Video/Palette/PRA7: IC79.17, IC80.9, IC81.9
/Video/Palette/PRA8: IC79.16, IC82.5, IC95.5
/Video/Palette/VALID: IC95.2, IC96.13
/Video/Palette/~MAxDD/E: IC37.13, IC75.1, IC75.19, IC82.19, IC96.8
/Video/Palette/~MAxDD: IC82.13, IC89.5, IC91.19, IC96.10
/Video/Palette/~MAxDD*: IC82.7, IC97.4
/Video/Palette/~MAxDE: IC80.1, IC80.19, IC82.11, IC89.6, IC94.19, IC96.9
/Video/Palette/~MAxDE*: IC82.9, IC97.1
/Video/Palette/~MAxDF: IC89.7, IC89.15
/Video/Palette/~SHAWE: IC97.2, IC97.5, IC97.9
/Video/Palette/~VCFG: IC46.11, IC97.8
/Video/Palette/~WE0: IC76.10, IC77.10, IC97.6
/Video/Palette/~WE1: IC78.10, IC79.10, IC97.3
/Video/Tile ROM/D0: IC8.11, IC9.11, IC10.11, IC11.11, IC13.6
/Video/Tile ROM/D1: IC8.12, IC9.12, IC10.12, IC11.12, IC13.5
/Video/Tile ROM/D2: IC8.13, IC9.13, IC10.13, IC11.13, IC13.4
/Video/Tile ROM/D3: IC8.15, IC9.15, IC10.15, IC11.15, IC13.3
/Video/Tile ROM/D4: IC8.16, IC9.16, IC10.16, IC11.16, IC23.6
/Video/Tile ROM/D5: IC8.17, IC9.17, IC10.17, IC11.17, IC23.5
/Video/Tile ROM/D6: IC8.18, IC9.18, IC10.18, IC11.18, IC23.4
/Video/Tile ROM/D7: IC8.19, IC9.19, IC10.19, IC11.19, IC23.3
/Video/Tile ROM/D8: IC12.6, IC32.11, IC33.11, IC34.11, IC35.11
/Video/Tile ROM/D9: IC12.5, IC32.12, IC33.12, IC34.12, IC35.12
/Video/Tile ROM/D10: IC12.4, IC32.13, IC33.13, IC34.13, IC35.13
/Video/Tile ROM/D11: IC12.3, IC32.15, IC33.15, IC34.15, IC35.15
/Video/Tile ROM/D12: IC22.6, IC32.16, IC33.16, IC34.16, IC35.16
/Video/Tile ROM/D13: IC22.5, IC32.17, IC33.17, IC34.17, IC35.17
/Video/Tile ROM/D14: IC22.4, IC32.18, IC33.18, IC34.18, IC35.18
/Video/Tile ROM/D15: IC22.3, IC32.19, IC33.19, IC34.19, IC35.19
/Video/Tile ROM/HFLIP: IC20.14, IC36.1
/Video/Tile ROM/S0: IC12.9, IC13.9, IC20.12, IC22.9, IC23.9
/Video/Tile ROM/S1: IC12.10, IC13.10, IC20.11, IC22.10, IC23.10
/Video/Tile ROM/VSS: IC8.14, IC9.14, IC10.14, IC11.14, IC12.2, IC12.7, IC13.2, IC13.7, IC20.15, IC22.2, IC22.7, IC23.2, IC23.7, IC32.14, IC33.14, IC34.14, IC35.14
/Video/Timing/V0: IC5.9, IC17.7, IC17.10, IC26.9
/Video/Timing/V1: IC16.2, IC17.14
/Video/Timing/V2: IC16.12, IC17.13
/Video/Timing/V3: IC16.5, IC17.12
/Video/Timing/V4: IC16.9, IC17.11, IC19.11
/Video/Timing/V5: IC25.3, IC26.2, IC27.14
/Video/Timing/V6: IC25.4, IC26.12, IC27.13
/Video/Timing/V7: IC25.5, IC26.5, IC27.12
/Video/Timing/V8: IC27.11, IC30.13
/Video/Timing/VC: IC17.15, IC27.7, IC27.10
/Video/Timing/~CLK6M: IC1.2, IC5.3, IC18.2, IC28.2, IC70.12
/Video/Timing/~H6: IC15.5, IC29.10
/Video/Timing/~VBL: IC3.3, IC19.9, IC25.2
/Video/VBL: IC19.8, IC24.11
/Video/VD0: IC7.3, IC62.3, IC86.9, IC90.11
/Video/VD1: IC7.4, IC62.4, IC86.10, IC90.12
/Video/VD2: IC7.9, IC62.9, IC86.11, IC90.13
/Video/VD3: IC7.7, IC15.9, IC62.7, IC86.13, IC90.14
/Video/VD4: IC15.13, IC21.3, IC54.18, IC86.14, IC90.15
/Video/VD5: IC21.4, IC54.17, IC86.15, IC90.16
/Video/VD6: IC21.9, IC54.14, IC86.16, IC90.17
/Video/VD7: IC21.7, IC54.13, IC86.17, IC90.18
/Video/VF0: IC26.8, IC41.18
/Video/VF1: IC16.3, IC41.3
/Video/VF2: IC16.11, IC41.14
/Video/VF3: IC16.6, IC41.4
/Video/VF4: IC16.8, IC41.17
/Video/VF5: IC26.3, IC41.7
/Video/VF6: IC26.11, IC41.13
/Video/VF7: IC26.6, IC41.8
/Video/Video RAM/CHBA0: IC20.2, IC61.15
/Video/Video RAM/CHBA1: IC20.3, IC61.14
/Video/Video RAM/D6': IC31.3, IC54.15
/Video/Video RAM/D7': IC31.4, IC54.12
/Video/Video RAM/SMX0: IC7.2, IC30.3
/Video/Video RAM/SMX1: IC7.1, IC30.8
/Video/Video RAM/~HB8: IC7.10, IC21.10, IC31.10, IC61.10
/Video/~CHA0: IC11.20, IC11.22, IC20.4, IC35.20, IC35.22
/Video/~CHA1: IC10.20, IC10.22, IC20.5, IC34.20, IC34.22
/Video/~CHA2: IC9.20, IC9.22, IC20.6, IC33.20, IC33.22
/Video/~CHA3: IC8.20, IC8.22, IC20.7, IC32.20, IC32.22
/Video/~CLK6*: IC2.2, IC49.1, IC49.19, IC65.10, IC66.10, IC67.10, IC82.1
/Video/~GHFLIP*: IC14.6, IC31.7
/Video/~HCRT: IC42.1, IC89.12
/Video/~HVLATCH: IC3.2, IC46.9
/Video/~MAxDC*: IC24.4, IC45.19, IC60.1, IC60.19, IC71.1, IC89.4
/Video/~OSCNHF: IC31.12, IC52.3
/Video/~OSCNHF*: IC50.1, IC51.1, IC52.2
/Video/~PH0: IC44.11, IC70.1
/Video/~PH1: IC14.3, IC24.3, IC43.11, IC69.14, IC70.2
/Video/~PH2: IC69.13, IC70.3
/Video/~PH3: IC29.5, IC54.11, IC70.4
/Video/~PH5: IC29.3, IC70.6
/Video/~PH6: IC53.10, IC70.7
/Video/~PH7: IC47.11, IC70.9
/Video/~PXLEN: IC36.15, IC47.15
/Video/~TRCRT: IC4.10, IC89.10
/Video/~VCRT: IC41.1, IC89.11
/~DW: B38.5, B38.10, IC25.12
/~MAxD0: B9.15, B17.11, B20.4
/~MAxD4: B20.5, M18.1, M18.15
/~MAxD8: B5.7, B6.7, B7.7, B13.7, B14.7, B15.7, B16.1, B16.15, B20.6
/~MAxDC: B20.7, IC83.15, IC84.15, IC85.15
/~MAxD: B20.1, B55.1
/~MCUINT: B12.8, B13.14, B54.2
/~MMxC: B19.17, B21.4, B38.4
/~MMxD: B21.5, B31.4, B55.11
/~MMxE: B21.6, B29.5
/~MMxF: B21.7, B29.4
/~MQxC: B18.13, B19.19, B27.19, B30.8, B36.12, B49.1, B50.1, B51.1, B55.12
/~MQxC*: B31.1, B34.1, B35.11, B36.9
/~MRD: B19.13, B39.21, B40.22, B41.22, B42.22, B47.5
/~MRST: B10.2, B10.13, B12.13, B32.4, B39.26, B54.28, M23.13
/~MSCrq: B18.10, B19.1, B26.19, B30.6, B36.2, B49.19, B50.19, B51.19, B55.8
/~MSpC: B17.5, B32.3, B33.1, B33.9
/~MSxC: B19.2, B33.4
/~MSxD: B31.15, B33.5
/~MSxE: B29.10, B33.6
/~MSxF: B29.9, B33.7
/~MWR: B27.1, B31.2, B39.22, B40.27, B41.27, B42.27, B47.3
/~SBNMI: B9.4, B22.17
/~SBRD: B19.6, B22.21, B23.22, B24.22, B25.22, B26.1
/~SBREQ: B22.19, B32.2
/~SBRST: B2.7, B10.1
/~SBWAIT: B22.24, B30.11
/~SBWR: B22.22, B23.27, B24.27, B31.17
/~SHARD: B9.14, B19.7, B19.14, B48.20, IC45.1, IC68.4, IC90.1, IC91.1, IC94.1, M18.13
/~SHAWE: B9.2, B31.3, B31.18, B48.21, IC71.11, IC83.14, M18.3
/~SPC0: B9.7, B12.10, B53.11
/~SPC1: B9.9, B10.12, B52.1
/~VRAM: B19.3, B19.18, IC37.1, IC83.1, IC84.1, IC85.1, IC90.19
/~WDOG: B9.6, B17.9
GND: B2.8, B5.8, B6.8, B7.8, B9.8, B12.7, B13.8, B14.8, B15.8, B22.29, B23.14, B24.14, B25.14, B34.7, B35.7, B36.7, B37.7, B39.29, B40.14, B41.14, B42.14, B46.7, B48.12, IC2.7, IC5.7, IC14.7, IC24.7, IC36.8, IC62.8, M8.14, M9.14, M10.14, M22.7, M26.7, M27.8, M30.7, M37.14, M38.14, M39.14, S35.7
unnamed: B3.3, B3.5
unnamed: B3.9, B3.11
unnamed: B3.2, B10.4
unnamed: B3.4, B10.5
unnamed: B3.10, B3.12, B10.9, B10.10
unnamed: B4.6, B11.12
unnamed: B8.6, B32.6
unnamed: B8.1, B8.8
unnamed: B8.12, B17.8
unnamed: B9.1, B17.10
unnamed: B11.2, UB11.4
unnamed: B10.11, B12.4
unnamed: B13.4, B16.11
unnamed: B16.12, UB11.3
unnamed: B17.2, B29.2
unnamed: B17.6, B29.13
unnamed: B17.12, B18.3
unnamed: B17.13, B18.12
unnamed: B18.4, B38.8
unnamed: B18.11, B38.6
unnamed: B19.4, B29.8
unnamed: B19.15, B29.6
unnamed: B19.9, B19.12
unnamed: B22.27, B38.2
unnamed: B10.3, B22.26
unnamed: B31.9, B31.12
unnamed: B31.7, B31.14
unnamed: B31.19, B36.5
unnamed: B32.10, U2.11
unnamed: B33.15, B45.10
unnamed: B18.8, B34.2
unnamed: B29.3, B34.4
unnamed: B18.6, B34.12
unnamed: B30.12, B34.9
unnamed: B30.5, B34.8, B35.4
unnamed: B29.11, B34.10
unnamed: B29.12, B35.5
unnamed: B37.4, B38.3
unnamed: B37.10, B38.11
unnamed: B39.23, B45.9
unnamed: B30.3, B39.24
unnamed: B45.2, B45.13
unnamed: B45.8, B46.2
unnamed: B45.12, B46.11
unnamed: B55.3, B55.10
unnamed: B55.2, B55.13
unnamed: IC1.11, IC1.12
unnamed: IC1.10, IC2.9, IC2.12
unnamed: IC1.1, IC2.1, IC2.6
unnamed: IC3.5, IC3.10
unnamed: IC3.11, IC29.12
unnamed: IC3.9, IC41.11, IC42.11
unnamed: IC3.8, IC4.9
unnamed: IC5.2, IC5.6
unnamed: IC5.8, IC5.12
unnamed: IC12.15, IC36.14
unnamed: IC12.12, IC36.13
unnamed: IC13.15, IC36.2
unnamed: IC13.12, IC36.3
unnamed: IC14.5, IC38.2, IC39.2, IC39.5, IC39.10, IC39.13
unnamed: IC15.8, IC38.4
unnamed: IC1.4, IC17.9, IC27.9
unnamed: IC18.15, IC28.10
unnamed: IC15.6, IC19.2
unnamed: IC19.6, IC30.12
unnamed: IC19.12, IC25.6
unnamed: IC15.3, IC20.13
unnamed: IC7.11, IC21.11, IC29.4, IC31.11
unnamed: IC22.15, IC36.11
unnamed: IC22.12, IC36.10
unnamed: IC23.15, IC36.5
unnamed: IC23.12, IC36.6
unnamed: IC24.5, IC69.6, IC69.11
unnamed: IC24.8, IC24.12
unnamed: IC1.3, IC27.15
unnamed: IC1.5, IC28.15
unnamed: IC1.6, IC28.9
unnamed: IC6.1, IC29.8
unnamed: IC37.2, IC68.5
unnamed: IC37.8, IC96.1
unnamed: IC37.9, IC40.6
unnamed: IC43.9, IC47.17
unnamed: IC43.12, IC47.18
unnamed: IC43.15, IC47.13
unnamed: IC50.9, IC51.9, IC97.11
unnamed: IC50.7, IC50.10, IC51.15
unnamed: IC56.7, IC57.9
unnamed: IC38.6, IC61.9
unnamed: IC15.11, IC61.7
unnamed: IC29.9, IC30.9, IC61.13
unnamed: IC6.5, IC6.10, IC6.12, IC30.1, IC61.12
unnamed: IC37.10, IC64.1
unnamed: IC53.8, IC71.10
unnamed: IC83.4, IC86.23
unnamed: IC83.7, IC86.22
unnamed: IC83.9, IC86.19
unnamed: IC83.12, IC86.21
unnamed: IC84.4, IC86.4
unnamed: IC84.7, IC86.3
unnamed: IC84.9, IC86.2
unnamed: IC84.12, IC86.1
unnamed: IC85.4, IC86.8
unnamed: IC85.7, IC86.7
unnamed: IC85.9, IC86.6
unnamed: IC85.12, IC86.5
unnamed: IC68.6, IC86.18
unnamed: IC68.3, IC87.6
unnamed: IC89.9, IC97.10
unnamed: IC25.8, IC92.1, IC93.1
unnamed: IC4.6, IC95.18
unnamed: M2.7, M5.5
unnamed: M2.9, M5.10
unnamed: M2.2, M2.15
unnamed: M2.10, M5.9
unnamed: M2.8, M5.4
unnamed: M3.7, M6.4
unnamed: M3.9, M6.9
unnamed: M3.10, M6.10
unnamed: M3.8, M6.5
unnamed: M14.2, MRB1.2
unnamed: M14.5, MRB1.3
unnamed: M14.6, MRB1.4
unnamed: M14.9, MRB1.5
unnamed: M14.12, MRB1.6
unnamed: M14.15, MRB1.7
unnamed: M14.16, MRB1.8
unnamed: M14.19, MRB1.9
unnamed: M16.2, M24.5
unnamed: M16.4, M16.14, M25.9
unnamed: M16.6, M16.12, M23.4, M25.6
unnamed: M20.4, M21.4, S36.1
unnamed: M20.11, M21.2
unnamed: M21.6, S36.3
unnamed: M21.9, M23.6
unnamed: M21.10, M22.6
unnamed: M23.5, M24.6
unnamed: M23.3, M26.3, M26.11
unnamed: M26.4, M26.9
unnamed: M27.1, S36.6
unnamed: M28.21, MRB5.2
unnamed: M28.20, MRB5.3
unnamed: M28.19, MRB5.4
unnamed: M28.18, MRB5.5
unnamed: M28.17, MRB4.2
unnamed: M28.16, MRB4.3
unnamed: M28.15, MRB4.4
unnamed: M28.14, MRB4.5
unnamed: M28.13, MRB3.2
unnamed: M28.12, MRB3.3
unnamed: M28.11, MRB3.4
unnamed: M28.10, MRB3.5
unnamed: M28.9, MRB2.2
unnamed: M28.8, MRB2.3
unnamed: M28.7, MRB2.4
unnamed: M28.6, MRB2.5
unnamed: M23.9, M30.6
unnamed: M23.10, M23.11, M30.1
unnamed: M30.11, S31.9
unnamed: M21.11, M30.13
unnamed: M31.6, S31.13
unnamed: M31.1, M32.8
unnamed: M32.6, M32.13
unnamed: M23.1, M23.2, M32.1, M35.9
unnamed: M35.2, M35.6
unnamed: M35.11, M36.8
unnamed: M35.8, M35.12, M36.13
unnamed: U1.6, U1.7
unnamed: B32.5, U1.3
VSS: B1.7, B3.7, B3.8, B4.8, B8.7, B10.7, B12.2, B12.12, B13.12, B14.3, B14.4, B16.5, B16.8, B17.7, B18.7, B19.10, B21.8, B21.15, B29.7, B30.7, B31.10, B32.7, B33.8, B35.2, B35.12, B37.12, B38.7, B45.7, B47.1, B47.13, B49.10, B50.10, B51.10, B54.1, B54.5, B54.7, B55.7, CR1.10, CR2.10, CR3.10, CR4.10, CR5.10, CR6.10, IC1.7, IC4.4, IC6.7, IC7.8, IC15.7, IC16.7, IC17.3, IC17.4, IC18.3, IC18.4, IC18.5, IC18.6, IC20.1, IC20.8, IC21.8, IC25.7, IC26.7, IC27.6, IC28.3, IC28.4, IC28.6, IC29.7, IC30.7, IC31.8, IC37.7, IC38.7, IC39.7, IC40.7, IC41.10, IC42.10, IC49.10, IC50.8, IC51.7, IC51.8, IC51.10, IC53.7, IC57.7, IC58.8, IC58.9, IC58.15, IC58.16, IC59.8, IC59.9, IC59.15, IC59.16, IC60.10, IC61.8, IC65.9, IC65.15, IC65.16, IC66.9, IC66.15, IC66.16, IC67.9, IC67.15, IC67.16, IC68.7, IC69.3, IC69.10, IC69.15, IC70.8, IC71.6, IC71.14, IC71.15, IC72.3, IC72.8, IC72.13, IC73.8, IC73.11, IC74.4, IC74.8, IC74.9, IC75.10, IC76.8, IC76.9, IC77.8, IC77.9, IC78.8, IC78.9, IC79.8, IC79.9, IC80.10, IC86.20, IC87.8, IC87.13, IC88.3, IC88.8, IC88.12, IC89.8, IC92.8, IC93.8, IC96.7, IC97.7, M1.3, M1.7, M2.1, M3.1, M4.7, M5.7, M6.7, M7.29, M11.12, M15.1, M16.8, M18.8, M19.4, M19.5, M20.8, M21.7, M22.2, M23.7, M24.2, M25.2, M25.12, M28.1, M28.24, M29.21, M31.2, M32.2, M32.12, MRB1.1, MRB2.1, MRB3.1, MRB4.1, MRB5.1, MRB6.1, MRB7.1, MRB8.1, MRB9.1, S31.7, S31.12, S32.7, S36.7, U1.1
